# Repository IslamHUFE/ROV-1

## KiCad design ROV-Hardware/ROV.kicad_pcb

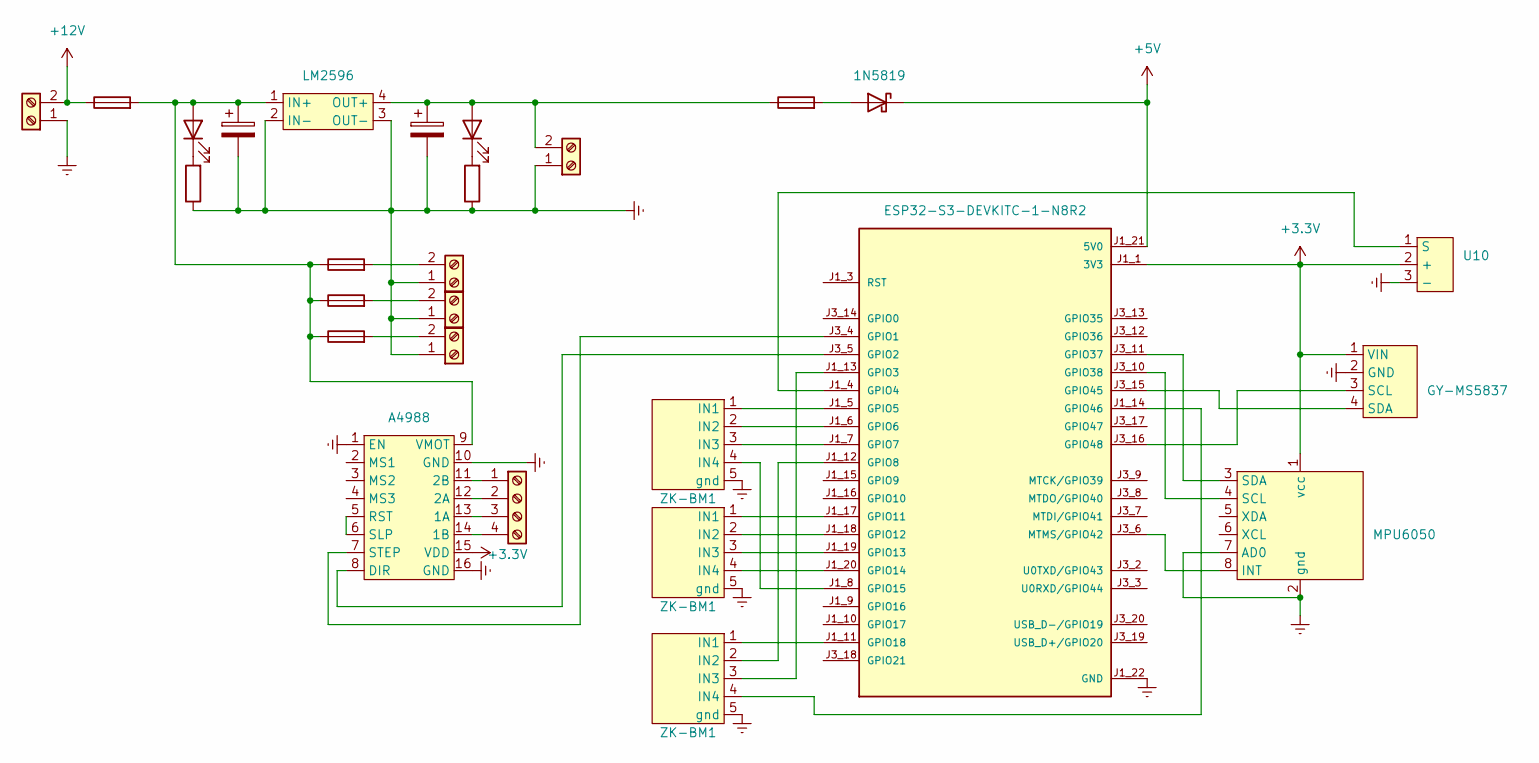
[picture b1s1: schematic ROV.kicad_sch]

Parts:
C1, C2: capacitor; CP_Radial_D5.0mm_P2.50mm
D1: 1N5819; D_DO-41_SOD81_P10.16mm_Horizontal
D2, D3: LED; LED_D3.0mm
F1, F2: fuse; Fuseholder_Clip-5x20mm_Schurter_CQM_Inline_P20.60x5.00mm_D1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
F3, F4, F5: fuse; Fuse_Blade_ATO_directSolder
J1: T-block; AMASS_XT60-F_1x02_P7.20mm_Vertical
J2, J4, J5, J6: T-block; TerminalBlock_MaiXu_MX126-5.0-02P_1x02_P5.00mm
J3: Screw_Terminal_01x04; TerminalBlock_MaiXu_MX126-5.0-04P_1x04_P5.00mm
R1, R2: R; R_Axial_DIN0204_L3.6mm_D1.6mm_P5.08mm_Horizontal
U1: LM2596; PinHeader_1x04_P2.54mm_Vertical
U3: ESP32-S3-DEVKITC-1-N8R2; XCVR_ESP32-S3-DEVKITC-1-N8R2; PARTREV V1
U4: MPU6050; PinHeader_1x08_P2.54mm_Vertical
U5, U6, U7: ZK-BM1; PinHeader_1x05_P2.54mm_Vertical
U8: A4988; Pololu_Breakout-16_15.2x20.3mm
U9: GY-MS5837; PinHeader_1x04_P2.54mm_Vertical
U10: PinHeader_1x03_P2.54mm_Vertical

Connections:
+3.3V: U3.J1_1 (3V3), U3.J1_2 (3V3), U4.1 (vcc), U8.15 (VDD), U9.1 (VIN), U10.2 (+)
+5V: D1.1 (K), U3.J1_21 (5V0)
+12V: F1.1, J1.2
GNDREF: C1.2, C2.2, J1.1, J2.1, J4.1, J5.1, J6.1, R1.1, R2.1, U1.2 (IN-), U1.3 (OUT-), U3.J1_22 (GND), U3.J3_1 (GND), U3.J3_21 (GND), U3.J3_22 (GND), U4.2 (gnd), U4.7 (AD0), U5.5 (gnd), U6.5 (gnd), U7.5 (gnd), U8.1 (EN), U8.10 (GND), U8.16 (GND), U9.2 (GND), U10.3 (-)
unnamed: D1.2 (A), F2.2
unnamed: C1.1, D2.2 (A), F1.2, F3.1, F4.1, F5.1, U1.1 (IN+), U8.9 (VMOT)
unnamed: D2.1 (K), R1.2
unnamed: C2.1, D3.2 (A), F2.1, J4.2, U1.4 (OUT+)
unnamed: D3.1 (K), R2.2
unnamed: F3.2, J2.2
unnamed: J3.1, U8.11 (2B)
unnamed: J3.2, U8.12 (2A)
unnamed: J3.3, U8.13 (1A)
unnamed: J3.4, U8.14 (1B)
unnamed: F4.2, J5.2
unnamed: F5.2, J6.2
unnamed: U3.J3_4 (GPIO1), U8.7 (STEP)
unnamed: U3.J3_5 (GPIO2), U8.8 (DIR)
unnamed: U3.J1_13 (GPIO3), U7.3 (IN3)
unnamed: U3.J1_5 (GPIO5), U6.1 (IN1)
unnamed: U3.J1_6 (GPIO6), U6.2 (IN2)
unnamed: U3.J1_7 (GPIO7), U6.3 (IN3)
unnamed: U3.J1_12 (GPIO8), U7.2 (IN2)
unnamed: U3.J1_17 (GPIO11), U5.1 (IN1)
unnamed: U3.J1_18 (GPIO12), U5.2 (IN2)
unnamed: U3.J1_19 (GPIO13), U5.3 (IN3)
unnamed: U3.J1_20 (GPIO14), U5.4 (IN4)
unnamed: U3.J1_8 (GPIO15), U6.4 (IN4)
unnamed: U3.J1_11 (GPIO18), U7.1 (IN1)
unnamed: U3.J3_11 (GPIO37), U4.3 (SDA)
unnamed: U3.J3_10 (GPIO38), U4.4 (SCL)
unnamed: U3.J3_15 (GPIO45), U9.4 (SDA)
unnamed: U3.J1_14 (GPIO46), U7.4 (IN4)
unnamed: U3.J3_16 (GPIO48), U9.3 (SCL)
unnamed: U3.J3_6 (MTMS/GPIO42), U4.8 (INT)
unnamed: U8.5 (RST), U8.6 (SLP)
unnamed: U3.J1_4 (GPIO4), U10.1 (S)

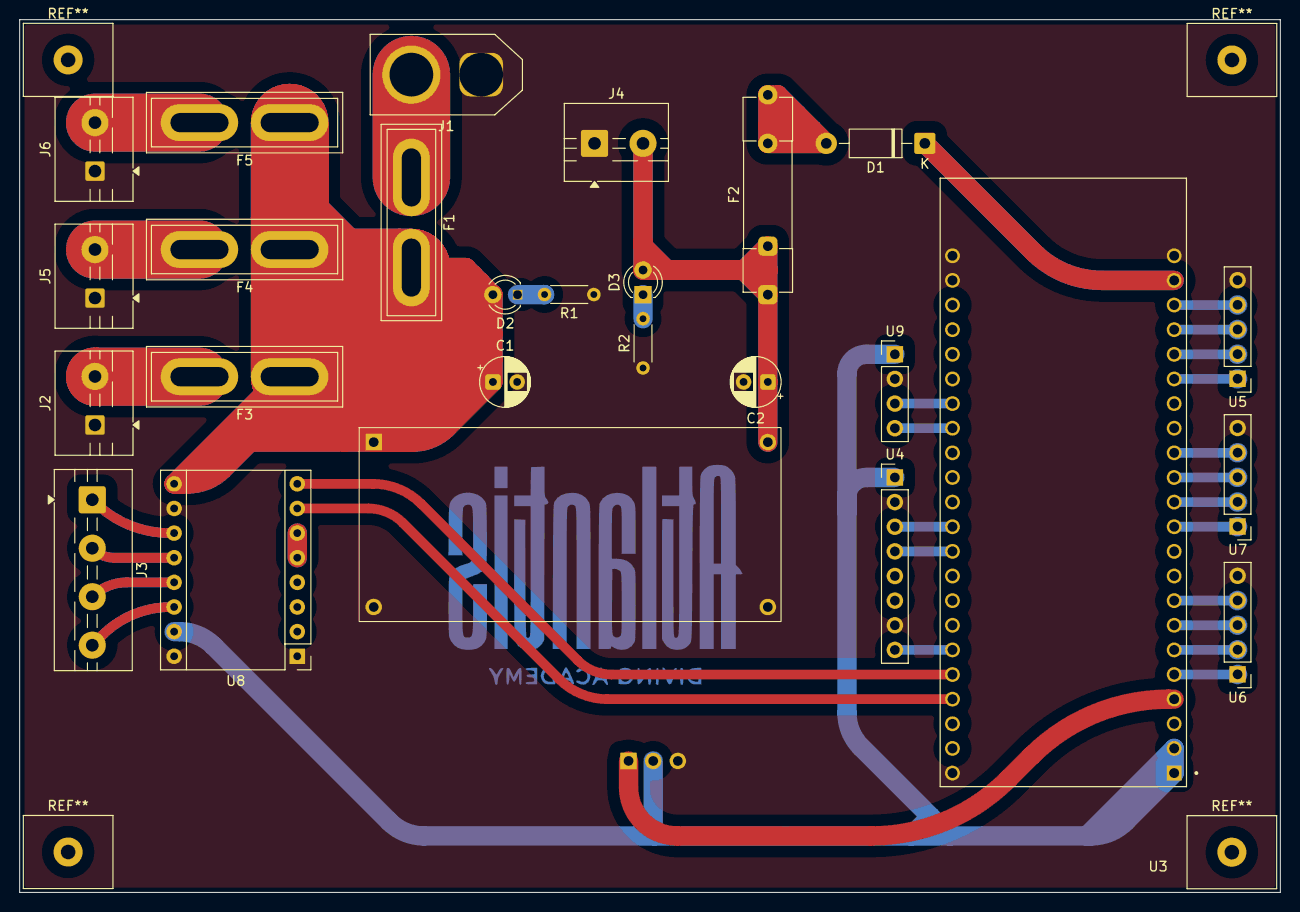
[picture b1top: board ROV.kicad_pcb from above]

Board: 2 copper layers, 130.0 x 90.0 mm, 27 parts (1 on the bottom side), 37 nets.

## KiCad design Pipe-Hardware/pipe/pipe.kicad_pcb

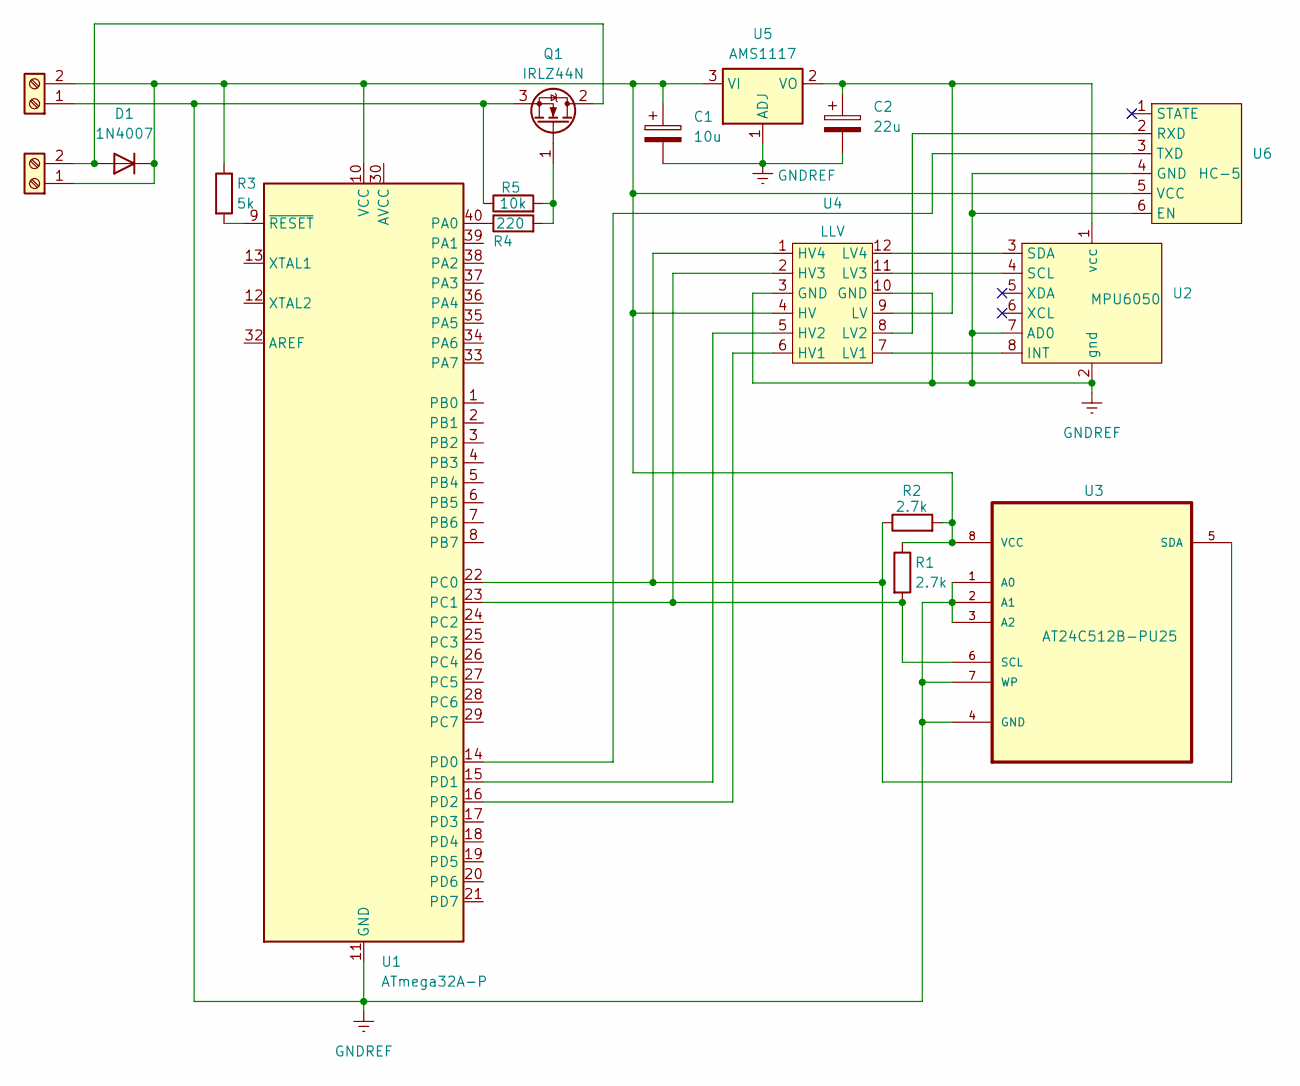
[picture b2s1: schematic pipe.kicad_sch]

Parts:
C1: 10u; CP_Radial_D8.0mm_P3.50mm
C2: 22u; CP_Radial_D8.0mm_P3.50mm
D1: 1N4007; D_DO-41_SOD81_P10.16mm_Horizontal
J1, J2: Screw_Terminal_01x02; TerminalBlock_MaiXu_MX126-5.0-02P_1x02_P5.00mm
Q1: IRLZ44N; TO-220-3_Vertical
R1, R2: 2.7k; R_Axial_DIN0204_L3.6mm_D1.6mm_P5.08mm_Horizontal
R3: 5k; R_Axial_DIN0204_L3.6mm_D1.6mm_P5.08mm_Horizontal
R4: 220; R_Axial_DIN0204_L3.6mm_D1.6mm_P5.08mm_Horizontal
R5: 10k; R_Axial_DIN0204_L3.6mm_D1.6mm_P5.08mm_Horizontal
U1: ATmega32A-P; DIP-40_W15.24mm
U2: MPU6050; PinHeader_1x08_P2.54mm_Vertical
U3: AT24C512B-PU25; DIP254P762X533-8; MPN AT24C512B-PU25
U4: LLV; DIP-12_W10.16mm_LongPads
U5: AMS1117; SOT-223-3_TabPin2
U6: HC-5; PinSocket_1x06_P2.54mm_Vertical

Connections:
GNDREF: C1.2, C2.2, J1.1, Q1.3 (S), R5.1, U1.11 (GND), U1.31 (GND), U2.2 (gnd), U2.7 (AD0), U3.1 (A0), U3.2 (A1), U3.3 (A2), U3.4 (GND), U3.7 (WP), U4.3 (GND), U4.10 (GND), U5.1 (ADJ), U6.4 (GND), U6.6 (EN)
unnamed: D1.2 (A), J2.2, Q1.2 (D)
unnamed: C1.1, D1.1 (K), J1.2, J2.1, R1.1, R2.2, R3.1, U1.10 (VCC), U3.8 (VCC), U4.4 (HV), U5.3 (VI), U6.5 (VCC)
unnamed: Q1.1 (G), R4.2, R5.2
unnamed: R4.1, U1.40 (PA0)
unnamed: R2.1, U1.22 (PC0), U3.5 (SDA), U4.1 (HV4)
unnamed: R1.2, U1.23 (PC1), U3.6 (SCL), U4.2 (HV3)
unnamed: U1.14 (PD0), U6.3 (TXD)
unnamed: U1.15 (PD1), U4.5 (HV2)
unnamed: U1.16 (PD2), U4.6 (HV1)
unnamed: R3.2, U1.9 (~RESET)
unnamed: U2.8 (INT), U4.7 (LV1)
unnamed: U2.4 (SCL), U4.11 (LV3)
unnamed: U2.3 (SDA), U4.12 (LV4)
unnamed: C2.1, U2.1 (vcc), U4.9 (LV), U5.2 (VO)
unnamed: U4.8 (LV2), U6.2 (RXD)

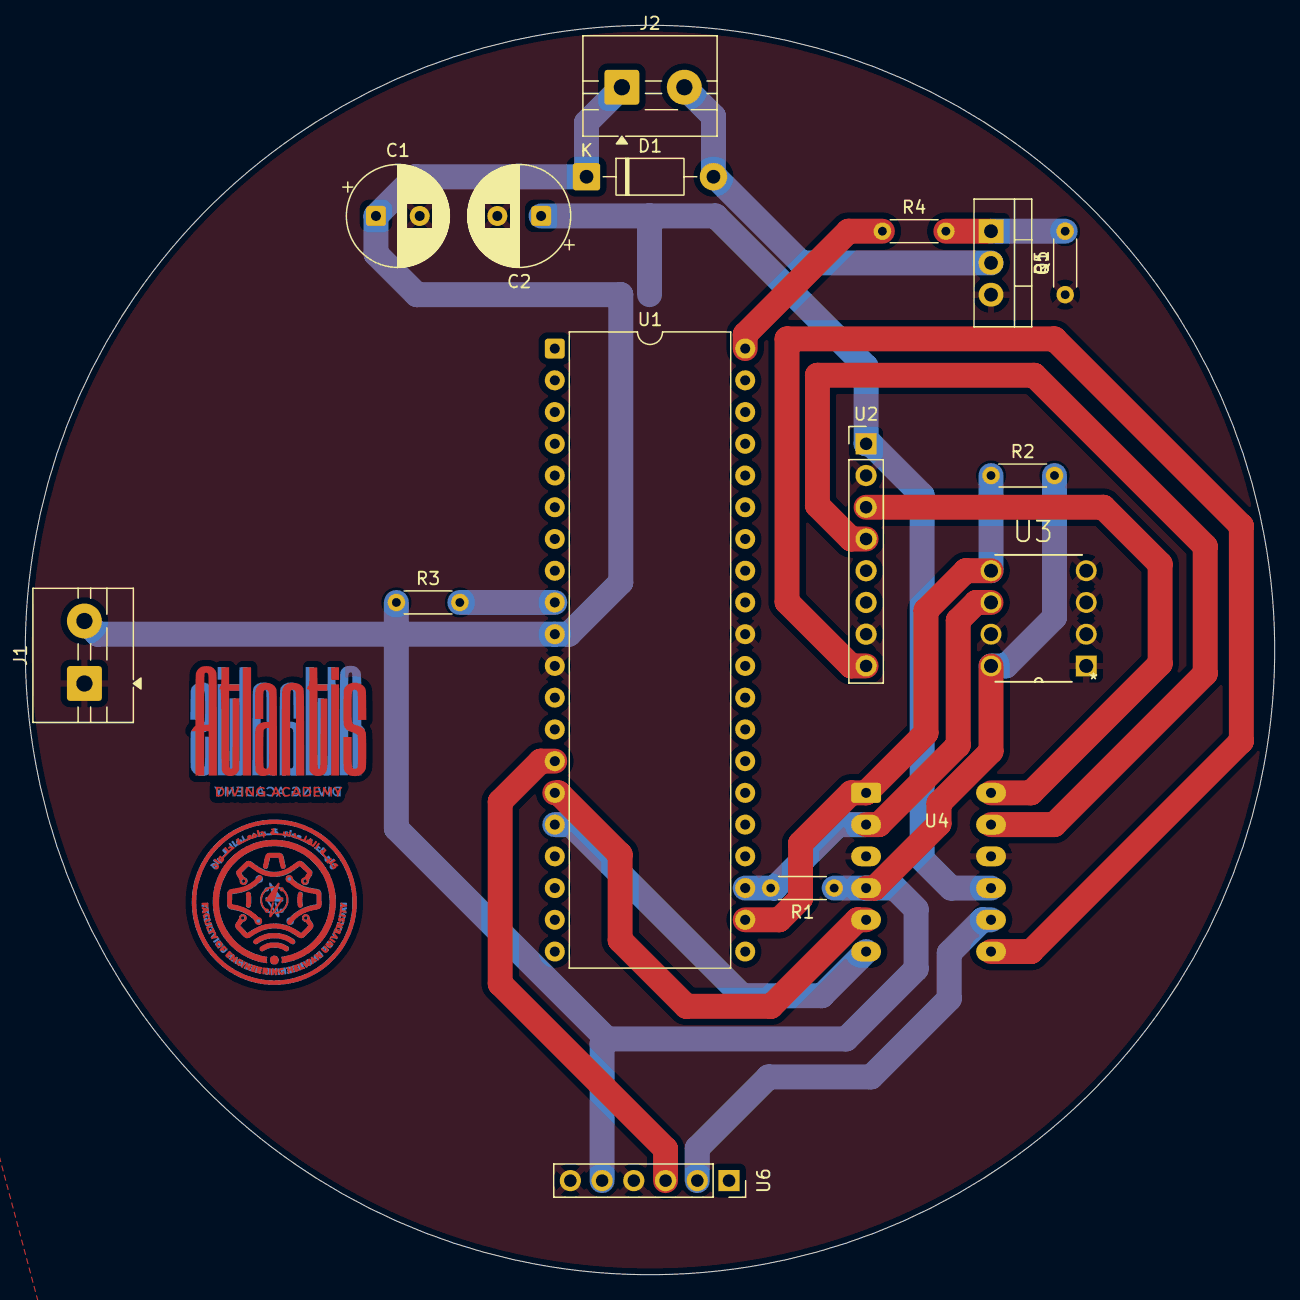
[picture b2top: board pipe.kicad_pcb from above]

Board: 2 copper layers, 100.0 x 100.0 mm, 17 parts (1 on the bottom side), 16 nets.

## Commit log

2026-02-24 Here i added my hardware branch
2026-02-28 Here I added layout.png
2026-03-01 Here I added the gallery
2026-03-05 Here I added GM-MS5837
2026-03-19 refresh
2026-03-22 moving controle file to ESP folder
2026-03-23 editing ground couting
2026-03-24 editing power and grounding tracks
2026-03-24 water sensor
2026-03-25 hight current
2026-03-26 edit SID
2026-03-27 gallery
2026-04-04 cylender
2026-04-04 تعديل الإسطوانة
2026-04-06 Fuse
2026-04-06 DC jack
2026-04-06 fishs and starfishs
2026-04-06 وجع القلب
2026-04-07 step converter
2026-04-08 pipe 2
2026-04-08 layout and some changes
